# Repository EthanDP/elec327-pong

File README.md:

# elec327-pong
pong pong pong pong pong pong pong pong pong pong pong pong pong pong pong pong pong pong pong pong pong pong pong pong pong pong pong pong pong pong pong pong pong pong pong pong pong pong pong pong pong pong pong pong pong pong pong pong pong pong pong pong pong pong pong pong pong pong pong pong pong pong pong

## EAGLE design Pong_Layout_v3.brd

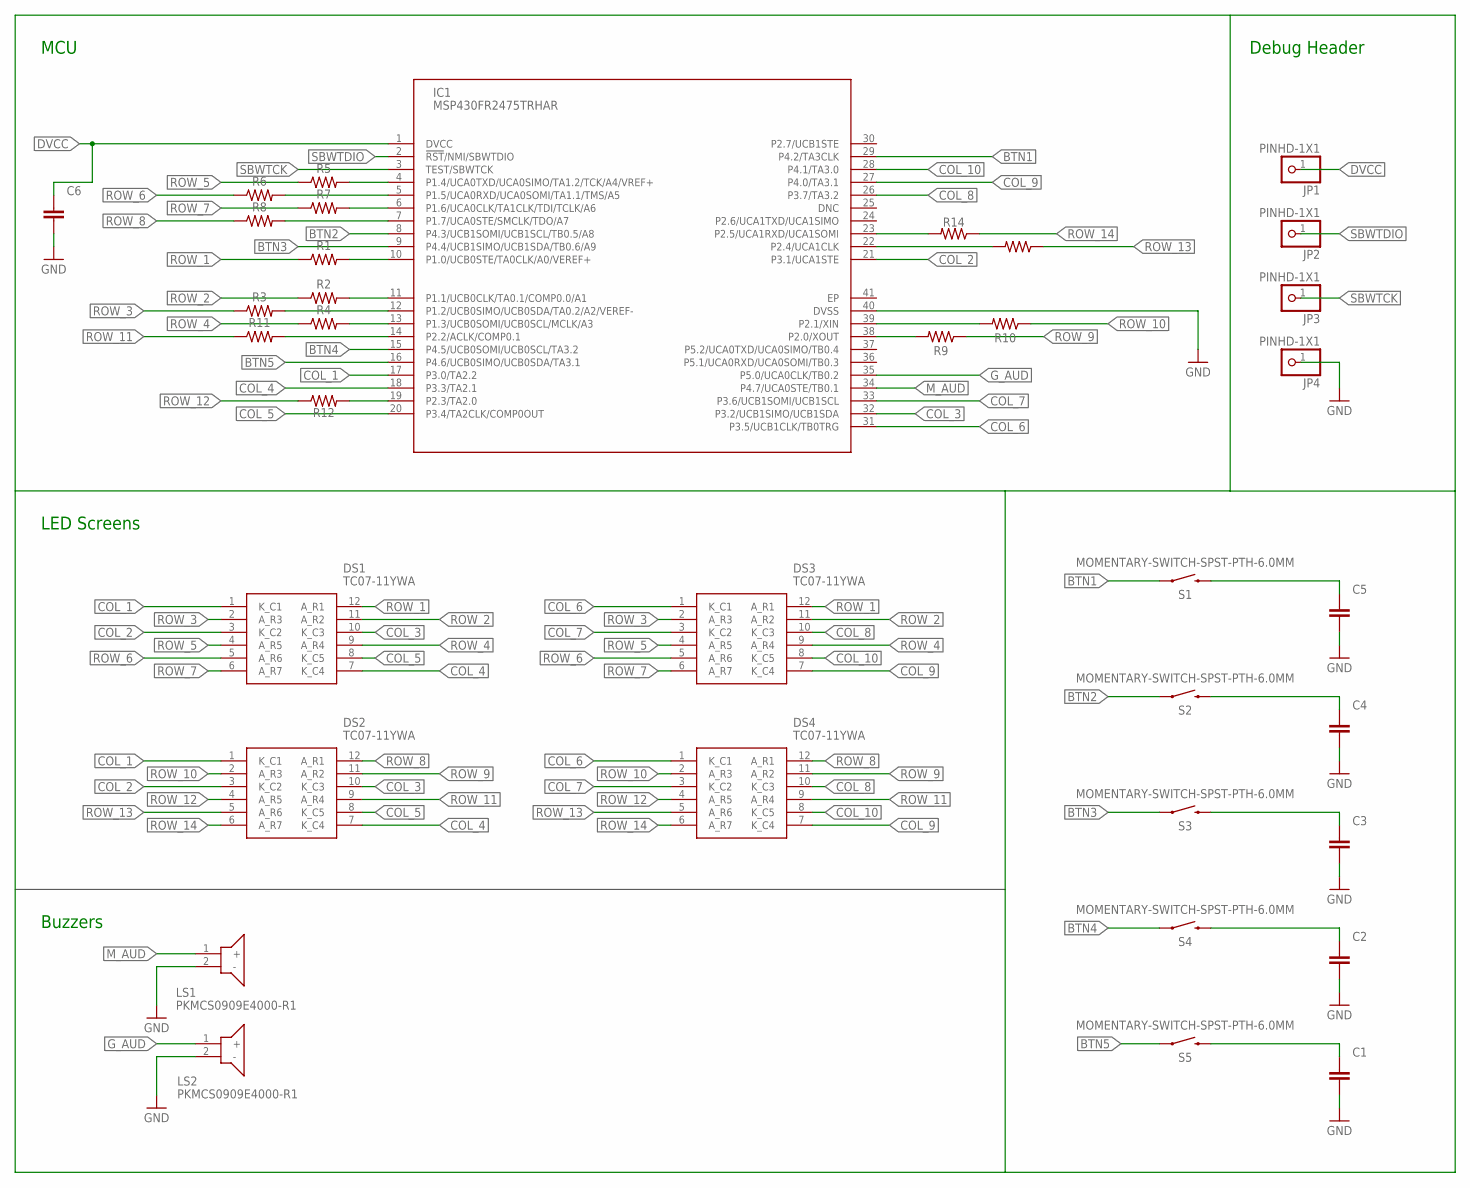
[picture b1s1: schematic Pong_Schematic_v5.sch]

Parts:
C1, C2, C3, C4, C5, C6: C_CHIP-0805(2012-METRIC); CAPC2012X110
DS1, DS2, DS3, DS4: TC07-11YWA; TC0711YWA
IC1: MSP430FR2475TRHAR; QFN50P600X600X100-41N
JP1, JP2, JP3, JP4: PINHD-1X1; 1X01
LS1, LS2: PKMCS0909E4000-R1; PKMCS0909E4000R1
R1, R2, R3, R4, R5, R6, R7, R8, R9, R10, R11, R12, R13, R14: R-US_CHIP-0805(2012-METRIC); RESC2012X65
S1, S2, S3, S4, S5: MOMENTARY-SWITCH-SPST-PTH-6.0MM; TACTILE_SWITCH_PTH_6.0MM

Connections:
BTN1: IC1.29 (P4.2/TA3CLK), S1.1
BTN2: IC1.8 (P4.3/UCB1SOMI/UCB1SCL/TB0.5/A8), S2.1
BTN3: IC1.9 (P4.4/UCB1SIMO/UCB1SDA/TB0.6/A9), S3.1
BTN4: IC1.15 (P4.5/UCB0SOMI/UCB0SCL/TA3.2), S4.1
BTN5: IC1.16 (P4.6/UCB0SIMO/UCB0SDA/TA3.1), S5.1
COL_1: DS1.1 (K_C1), DS2.1 (K_C1), IC1.17 (P3.0/TA2.2)
COL_2: DS1.3 (K_C2), DS2.3 (K_C2), IC1.21 (P3.1/UCA1STE)
COL_3: DS1.10 (K_C3), DS2.10 (K_C3), IC1.32 (P3.2/UCB1SIMO/UCB1SDA)
COL_4: DS1.7 (K_C4), DS2.7 (K_C4), IC1.18 (P3.3/TA2.1)
COL_5: DS1.8 (K_C5), DS2.8 (K_C5), IC1.20 (P3.4/TA2CLK/COMP0OUT)
COL_6: DS3.1 (K_C1), DS4.1 (K_C1), IC1.31 (P3.5/UCB1CLK/TB0TRG)
COL_7: DS3.3 (K_C2), DS4.3 (K_C2), IC1.33 (P3.6/UCB1SOMI/UCB1SCL)
COL_8: DS3.10 (K_C3), DS4.10 (K_C3), IC1.26 (P3.7/TA3.2)
COL_9: DS3.7 (K_C4), DS4.7 (K_C4), IC1.27 (P4.0/TA3.1)
COL_10: DS3.8 (K_C5), DS4.8 (K_C5), IC1.28 (P4.1/TA3.0)
DVCC: C6.1, IC1.1 (DVCC), JP1.1
GND: C1.2, C2.2, C3.2, C4.2, C5.2, C6.2, IC1.40 (DVSS), JP4.1, LS1.2 (-), LS2.2 (-)
G_AUD: IC1.35 (P5.0/UCA0CLK/TB0.2), LS2.1 (+)
M_AUD: IC1.34 (P4.7/UCA0STE/TB0.1), LS1.1 (+)
unnamed: IC1.10 (P1.0/UCB0STE/TA0CLK/A0/VEREF+), R1.2
unnamed: IC1.11 (P1.1/UCB0CLK/TA0.1/COMP0.0/A1), R2.2
unnamed: IC1.12 (P1.2/UCB0SIMO/UCB0SDA/TA0.2/A2/VEREF-), R3.2
unnamed: IC1.13 (P1.3/UCB0SOMI/UCB0SCL/MCLK/A3), R4.2
unnamed: IC1.4 (P1.4/UCA0TXD/UCA0SIMO/TA1.2/TCK/A4/VREF+), R5.2
unnamed: IC1.5 (P1.5/UCA0RXD/UCA0SOMI/TA1.1/TMS/A5), R6.2
unnamed: IC1.6 (P1.6/UCA0CLK/TA1CLK/TDI/TCLK/A6), R7.2
unnamed: IC1.7 (P1.7/UCA0STE/SMCLK/TDO/A7), R8.2
unnamed: IC1.38 (P2.0/XOUT), R9.2
unnamed: IC1.39 (P2.1/XIN), R10.2
unnamed: IC1.14 (P2.2/ACLK/COMP0.1), R11.2
unnamed: IC1.19 (P2.3/TA2.0), R12.2
unnamed: IC1.22 (P2.4/UCA1CLK), R13.2
unnamed: IC1.23 (P2.5/UCA1RXD/UCA1SOMI), R14.2
unnamed: C1.1, S5.3 (2)
unnamed: C2.1, S4.3 (2)
unnamed: C3.1, S3.3 (2)
unnamed: C4.1, S2.3 (2)
unnamed: C5.1, S1.3 (2)
ROW_1: DS1.12 (A_R1), DS3.12 (A_R1), R1.1
ROW_2: DS1.11 (A_R2), DS3.11 (A_R2), R2.1
ROW_3: DS1.2 (A_R3), DS3.2 (A_R3), R3.1
ROW_4: DS1.9 (A_R4), DS3.9 (A_R4), R4.1
ROW_5: DS1.4 (A_R5), DS3.4 (A_R5), R5.1
ROW_6: DS1.5 (A_R6), DS3.5 (A_R6), R6.1
ROW_7: DS1.6 (A_R7), DS3.6 (A_R7), R7.1
ROW_8: DS2.12 (A_R1), DS4.12 (A_R1), R8.1
ROW_9: DS2.11 (A_R2), DS4.11 (A_R2), R9.1
ROW_10: DS2.2 (A_R3), DS4.2 (A_R3), R10.1
ROW_11: DS2.9 (A_R4), DS4.9 (A_R4), R11.1
ROW_12: DS2.4 (A_R5), DS4.4 (A_R5), R12.1
ROW_13: DS2.5 (A_R6), DS4.5 (A_R6), R13.1
ROW_14: DS2.6 (A_R7), DS4.6 (A_R7), R14.1
SBWTCK: IC1.3 (TEST/SBWTCK), JP3.1
SBWTDIO: IC1.2 (!RST!/NMI/SBWTDIO), JP2.1

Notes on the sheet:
MCU
Debug Header
LED Screens
Buzzers

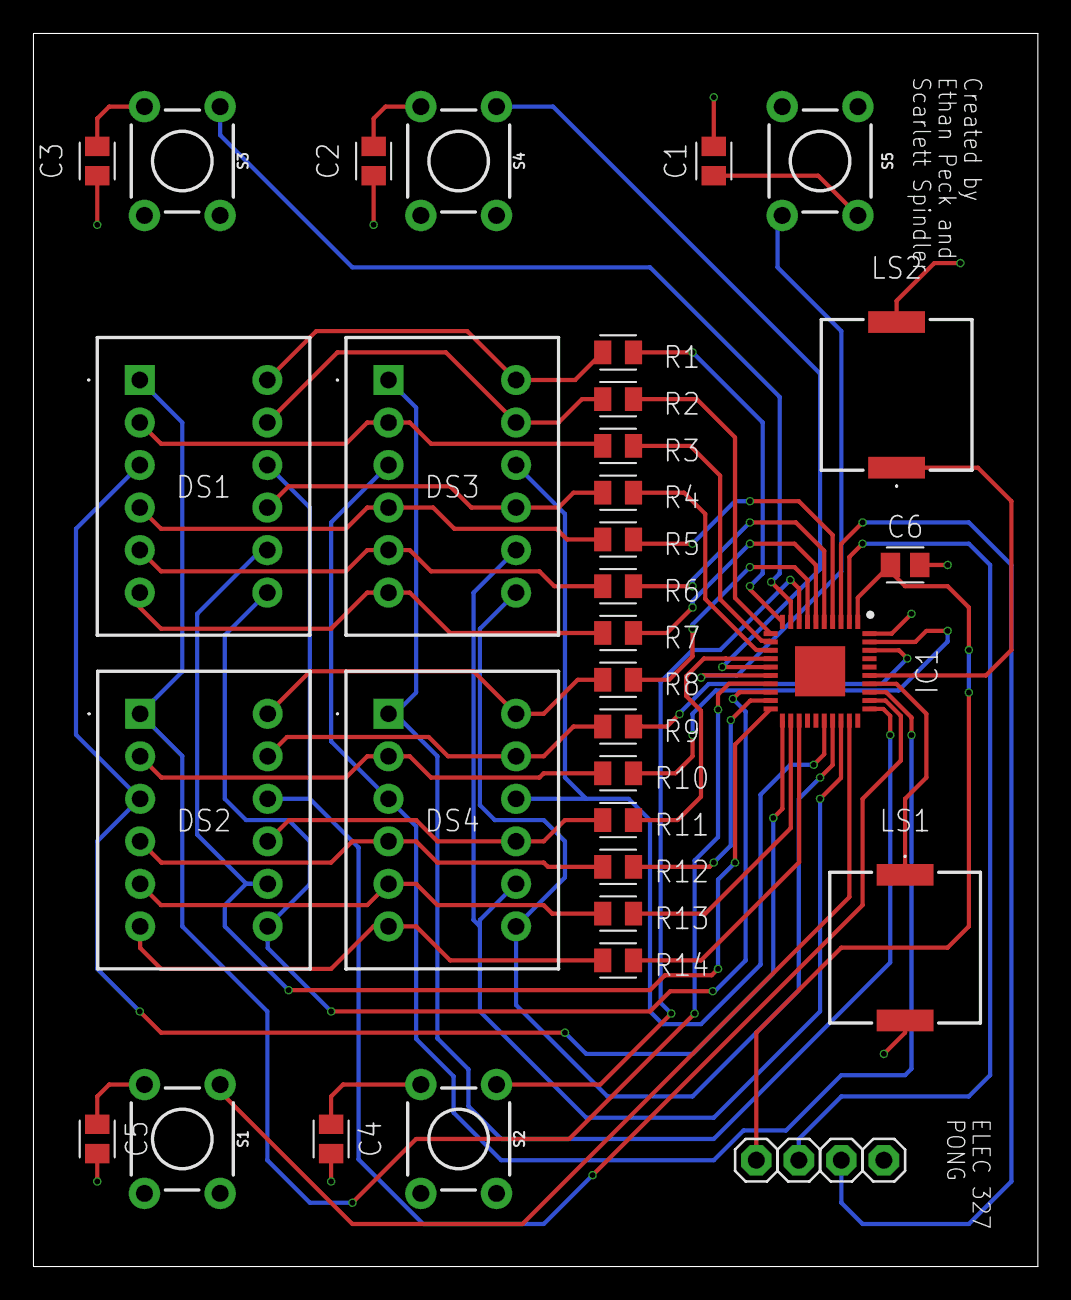
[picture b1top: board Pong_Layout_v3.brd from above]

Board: 2 copper layers, 60.0 x 73.7 mm, 36 parts (0 on the bottom side), 54 nets.

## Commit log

2023-05-03 Add hardware files
2023-05-03 I forgor to commit to github

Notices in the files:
parts and their libraries:
SparkFun-Switches: Licensing: Creative Commons ShareAlike 4.0 International - https://creativecommons.org/licenses/by-sa/4.0
